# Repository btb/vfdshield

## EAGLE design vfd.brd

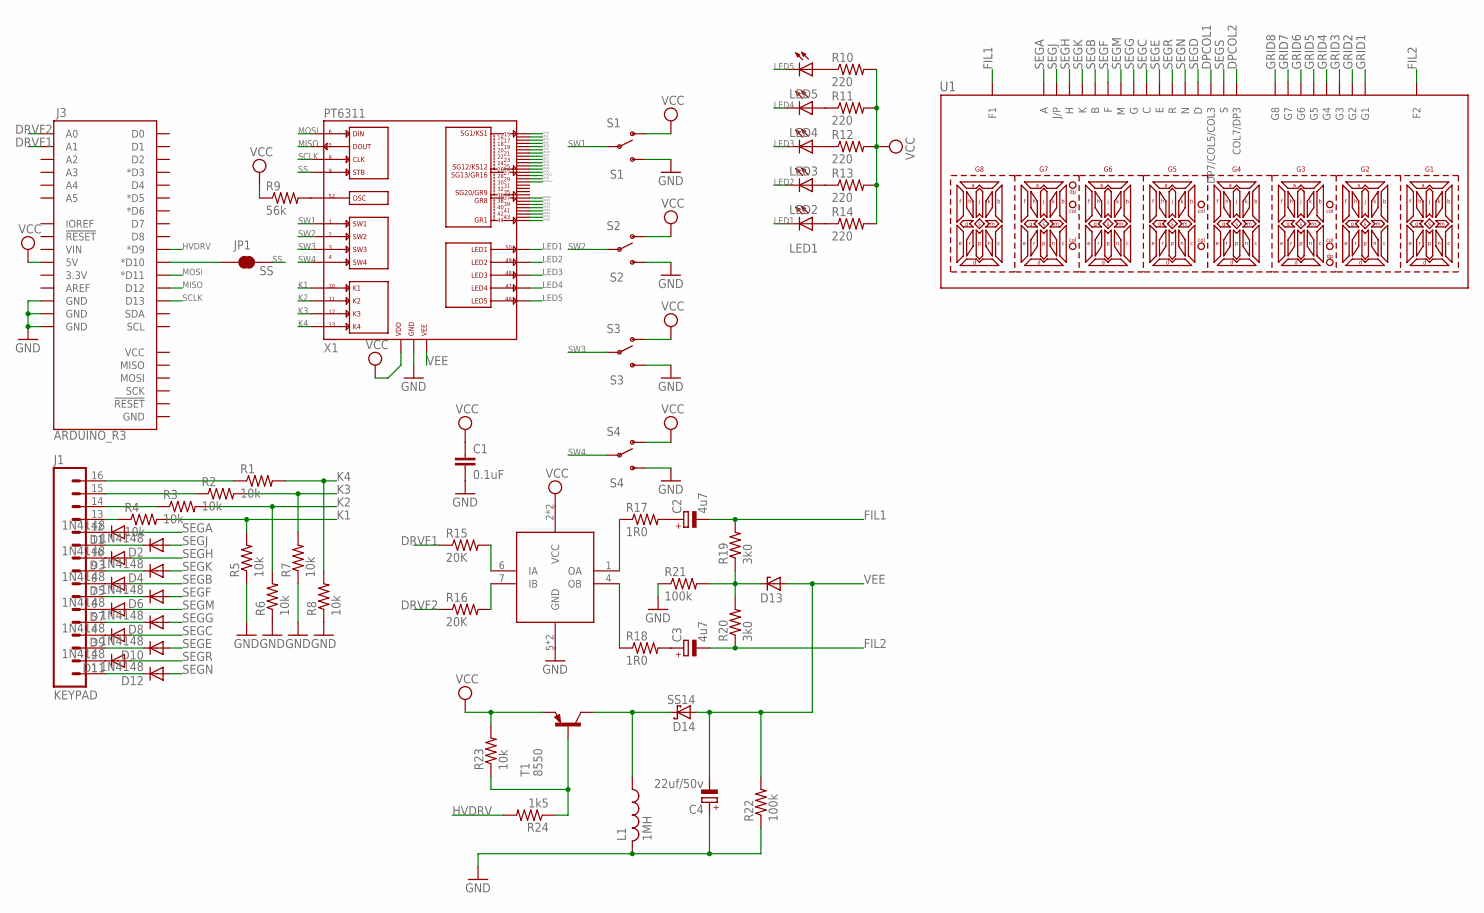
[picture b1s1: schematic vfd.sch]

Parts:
C1: 0.1uF; C050-025X075
C2, C3: 4u7; B45181A
C4: 22uf/50v; B45181A
D1, D2, D3, D4, D5, D6, D7, D8, D9, D10, D11, D12: 1N4148; D-5
D13: ZENER-DIODEDO34-7; DO34Z7
D14: SS14; DO35-7
J1: KEYPAD; 1X16
J3: ARDUINO_R3
JP1: SS; PAD-JUMPER-2-NC_BY_TRACE_YES_SILK
L1: 1MH; 0204/5
LED1: LED1; LED3MM
LED2: LED2; LED3MM
LED3: LED3; LED3MM
LED4: LED4; LED3MM
LED5: LED5; LED3MM
R1, R2, R3, R4: 10k; 0204/7
R5, R6, R7, R8, R23: 10k; 0204/5
R9: 56k; 0204/5
R10, R11, R12, R13, R14: 220; 0204/5
R15, R16: 20K; 0204/5
R17, R18: 1R0; 0204/5
R19, R20: 3k0; 0204/7
R21: 100k; 0204/7
R22: 100k; 0204/5
R24: 1k5; 0204/5
S1: S1; SWITCH-SPDT
S2: S2; SWITCH-SPDT
S3: S3; SWITCH-SPDT
S4: S4; SWITCH-SPDT
T1: 8550; TO92
U1: 20070-1A04PTH; 20070-1A04
U$1: L9110; SOP8-1.27-5X3.6MM
X1: DRV; QFP52

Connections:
DPCOL1: U1.17 (DP7/COL5/COL3), X1.P$28 (SG14/GR15)
DPCOL2: U1.19 (COL7/DP3), X1.P$30 (SG16/GR13)
DRVF1: J3.A1, R15.1
DRVF2: J3.A0, R16.1
FIL1: C2.-, R19.2, U1.1 (F1), U1.2 (F1)
FIL2: C3.-, R20.1, U1.29 (F2), U1.30 (F2)
GND: C1.2, C4.+, J3.GND@2 (GND), J3.GND@3 (GND), J3.GND@4 (GND), L1.2, R5.1, R6.1, R7.1, R8.1, R21.1, R22.1, S1.3 (S), S2.3 (S), S3.3 (S), S4.3 (S), U$1.5 (GND), U$1.8 (GND), X1.P$51 (GND)
GRID1: U1.27 (G1), X1.P$44 (GR1)
GRID2: U1.26 (G2), X1.P$43 (GR2)
GRID3: U1.25 (G3), X1.P$42 (GR3)
GRID4: U1.24 (G4), X1.P$41 (GR4)
GRID5: U1.23 (G5), X1.P$40 (GR5)
GRID6: U1.22 (G6), X1.P$39 (GR6)
GRID7: U1.21 (G7), X1.P$38 (GR7)
GRID8: U1.20 (G8), X1.P$37 (GR8)
HVDRV: J3.D9 (*D9), R24.2
K1: R4.2, R5.2, X1.P$10 (K1)
K2: R3.2, R6.2, X1.P$11 (K2)
K3: R2.2, R7.2, X1.P$12 (K3)
K4: R1.2, R8.2, X1.P$13 (K4)
LED1: LED1.K (C), X1.P$50 (LED1)
LED2: LED2.K (C), X1.P$49 (LED2)
LED3: LED3.K (C), X1.P$48 (LED3)
LED4: LED4.K (C), X1.P$47 (LED4)
LED5: LED5.K (C), X1.P$46 (LED5)
MISO: J3.D12, X1.P$5 (DOUT)
MOSI: J3.D11 (*D11), X1.P$6 (DIN)
unnamed: D1.C, J1.12
unnamed: D2.C, J1.11
unnamed: D3.C, J1.10
unnamed: D4.C, J1.9
unnamed: D5.C, J1.8
unnamed: D6.C, J1.7
unnamed: D7.C, J1.6
unnamed: D8.C, J1.5
unnamed: D9.C, J1.4
unnamed: D10.C, J1.3
unnamed: D11.C, J1.2
unnamed: D12.C, J1.1
unnamed: J1.16, R1.1
unnamed: J1.15, R2.1
unnamed: J1.14, R3.1
unnamed: J1.13, R4.1
unnamed: J3.D10 (*D10), JP1.1
unnamed: R9.2, X1.P$52 (OSC)
unnamed: LED5.A, R10.1
unnamed: LED4.A, R11.1
unnamed: LED3.A, R12.1
unnamed: LED2.A, R13.1
unnamed: LED1.A, R14.1
unnamed: R15.2, U$1.6 (IA)
unnamed: R16.2, U$1.7 (IB)
unnamed: R17.1, U$1.1 (OA)
unnamed: R18.1, U$1.4 (OB)
unnamed: C2.+, R17.2
unnamed: C3.+, R18.2
unnamed: D13.C, R19.1, R20.2, R21.2
unnamed: R23.1, R24.1, T1.2 (B)
unnamed: D14.C, L1.1, T1.3 (C)
SCLK: J3.D13, X1.P$8 (CLK)
SEGA: D1.A, U1.4 (A), X1.P$15 (SG1/KS1)
SEGB: D5.A, U1.8 (B), X1.P$19 (SG5/KS5)
SEGC: D9.A, U1.12 (C), X1.P$23 (SG9/KS9)
SEGD: U1.16 (D), X1.P$27 (SG13/GR16)
SEGE: D10.A, U1.13 (E), X1.P$24 (SG10/KS10)
SEGF: D6.A, U1.9 (F), X1.P$20 (SG6/KS6)
SEGG: D8.A, U1.11 (G), X1.P$22 (SG8/KS8)
SEGH: D3.A, U1.6 (H), X1.P$17 (SG3/KS3)
SEGJ: D2.A, U1.5 (J/P), X1.P$16 (SG2/KS2)
SEGK: D4.A, U1.7 (K), X1.P$18 (SG4/KS4)
SEGM: D7.A, U1.10 (M), X1.P$21 (SG7/KS7)
SEGN: D12.A, U1.15 (N), X1.P$26 (SG12/KS12)
SEGR: D11.A, U1.14 (R), X1.P$25 (SG11/KS11)
SEGS: U1.18 (S), X1.P$29 (SG15/GR14)
SS: JP1.2, X1.P$9 (STB)
SW1: S1.2, X1.P$1 (SW1)
SW2: S2.2, X1.P$2 (SW2)
SW3: S3.2, X1.P$3 (SW3)
SW4: S4.2, X1.P$4 (SW4)
VCC: C1.1, J3.5V, R9.1, R10.2, R11.2, R12.2, R13.2, R14.2, R23.2, S1.1 (O), S2.1 (O), S3.1 (O), S4.1 (O), T1.1 (E), U$1.2 (VCC), U$1.3 (VCC), X1.P$14 (VDD), X1.P$33 (VDD), X1.P$45 (VDD)
VEE: C4.-, D13.A, D14.A, R22.2, X1.P$34 (VEE)

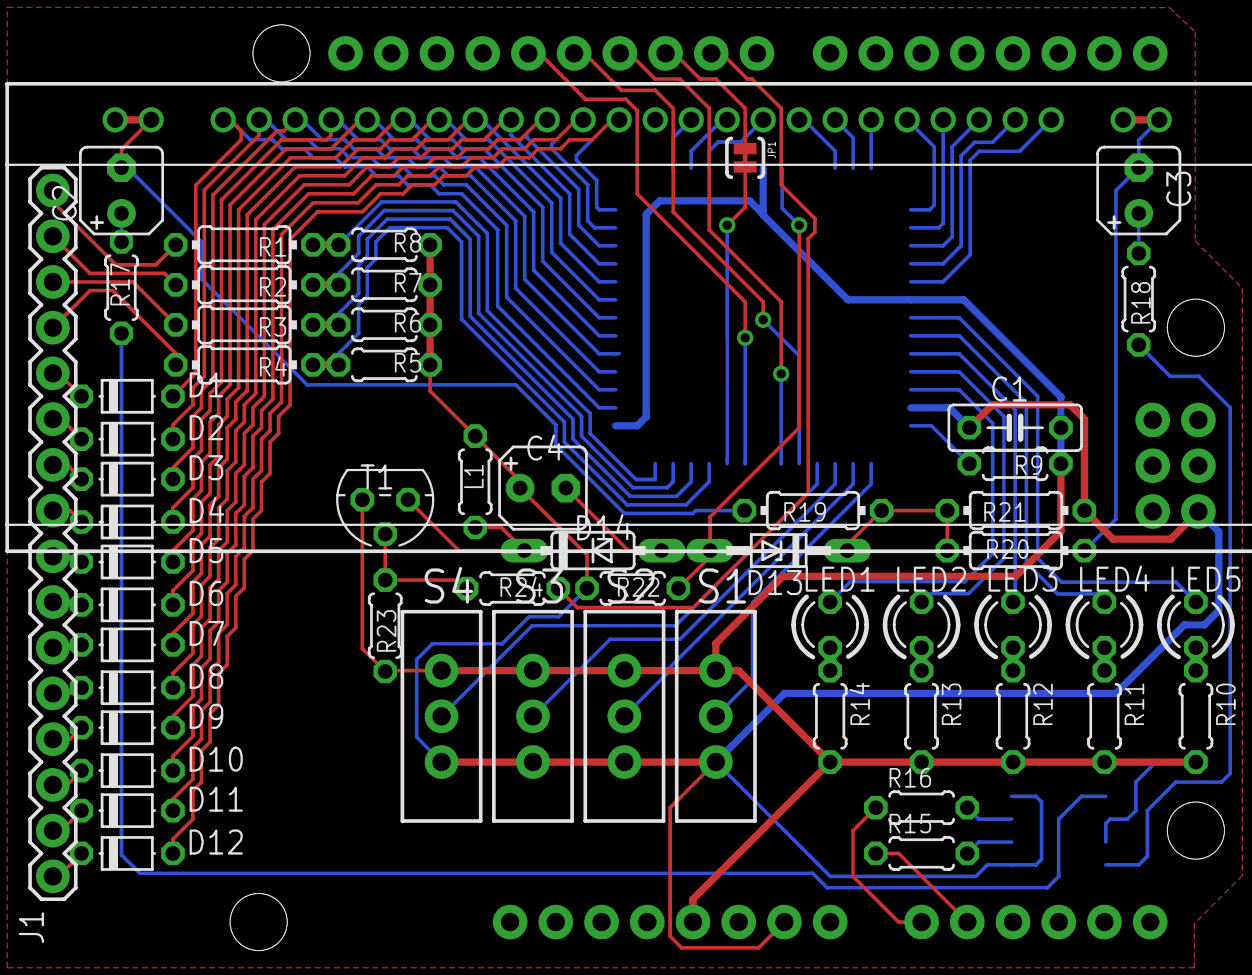
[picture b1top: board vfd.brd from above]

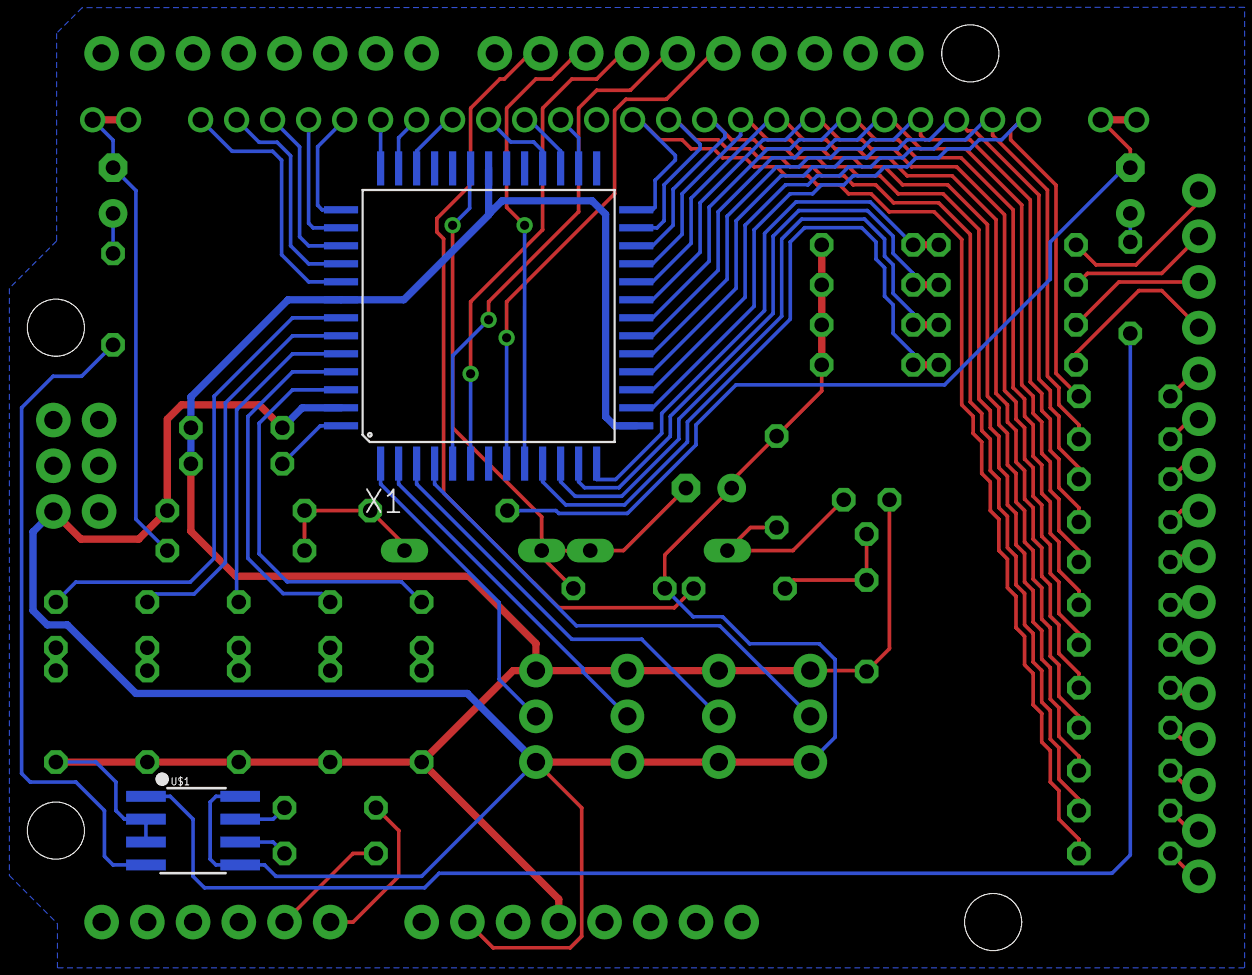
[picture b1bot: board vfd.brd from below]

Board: 2 copper layers, 59 parts (2 on the bottom side), 81 nets.

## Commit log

2016-07-11 ignore
2016-07-12 add filament driver components
2016-07-14 all lines laid
2016-07-26 shape ground planes to match shield

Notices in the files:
parts and their libraries:
SparkFun-Connectors: Licensing: Creative Commons ShareAlike 4.0 International - https://creativecommons.org/licenses/by-sa/4.0
